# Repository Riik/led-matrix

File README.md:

# rpi-led-matrix
Python / C control for a LED matrix

# Goal
Create the software for a hardware project which can drive a LED matrix with a extendable number of rows and columns

# Hardware
To drive the rows, the MIC2981 driver IC is used. It can source up to 500mA per pin, which mean 25 columns @ 20mA / column.
To sink the columns, the TPIC6C595 is used. I needs to be able to sink one column (20mA) per pin, so for an 8 bit shift register the total IC must be able to sink 8*20mA. The TPIC6C595 is able to sink up to 100mA per pin.
The rows should multiplexed, i.e. they should not be one at the same time.

# Software
Suitable candidates:
  - PIGpio Python library using DMA control http://abyz.me.uk/rpi/pigpio/
  - Directly talking to SPI hardware in C using IOCTL

# Notes to selfs
  - If multiple rows are active, current is split / LEDS are in parallel with respect to the sinking column.
  - We probably need a resistor per sink / column

# On the subject of the LED matrix 3D model
For this model, we use two programs: OpenSCAD and FreeCAD. OpenSCAD is used to program the model. To make the model readable for KiCad:
1. Open FreeCAD
2. Select View->Workbench->OpenSCAD
3. Open the *.scad file (File->Open)
4. In Combo View->Model->Labels & Attributes->2088BS select union
5. Go to File->Export
6. Export the model as a STEP with colors (*.step *.stp)

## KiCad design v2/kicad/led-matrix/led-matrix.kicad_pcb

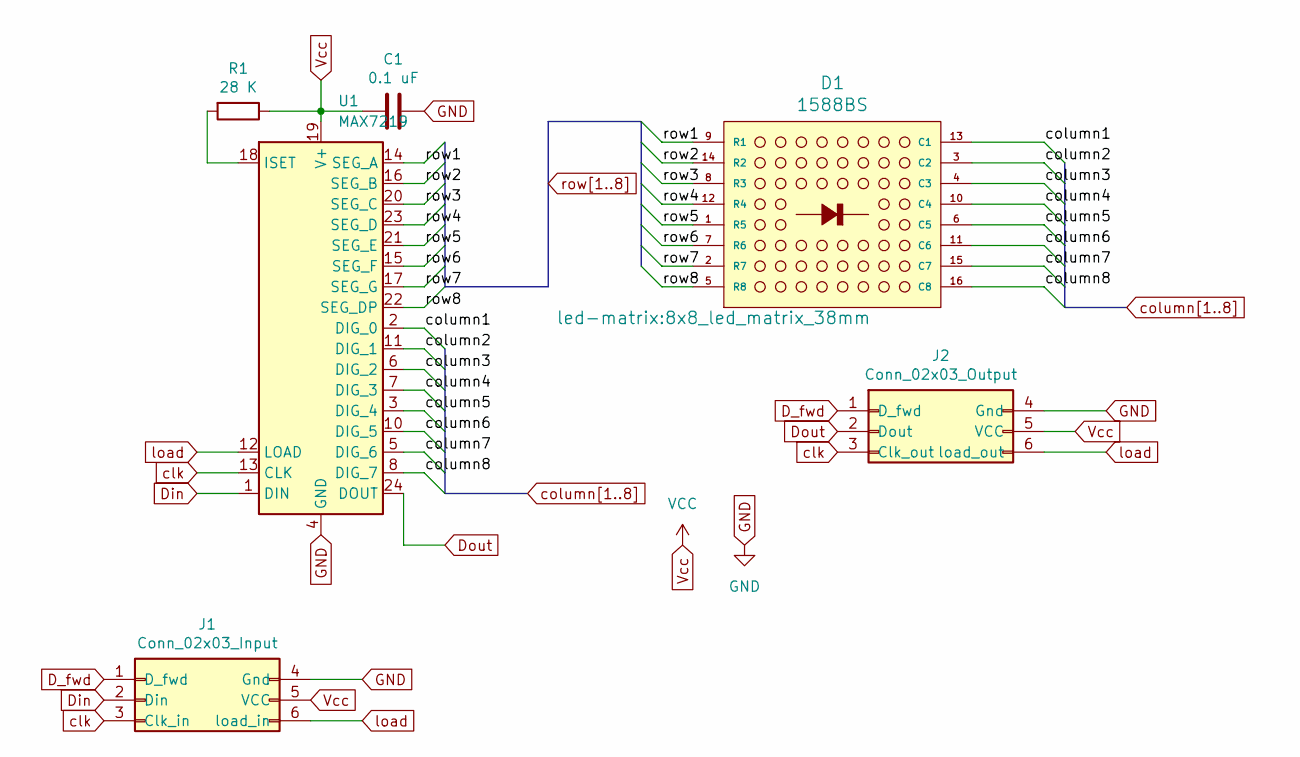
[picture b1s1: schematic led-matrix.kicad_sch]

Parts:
C1: 0.1 uF; C_1206_3216Metric_Pad1.33x1.80mm_HandSolder
D1: 1588BS; 8x8_led_matrix_38mm
J1: Conn_02x03_Input; PinSocket_2x03_P2.54mm_Horizontal
J2: Conn_02x03_Output; PinHeader_2x03_P2.54mm_Horizontal
R1: 28 K; R_1206_3216Metric_Pad1.30x1.75mm_HandSolder
U1: MAX7219; HandSolder.SOIC-24W_7.5x15.4mm_P1.27mm

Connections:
D_fwd: J1.1 (D_fwd), J2.1 (D_fwd)
Din: J1.2 (Din), U1.1 (DIN)
Dout: J2.2 (Dout), U1.24 (DOUT)
GND: C1.1, J1.4 (Gnd), J2.4 (Gnd), U1.4 (GND), U1.9 (GND)
unnamed: R1.2, U1.18 (ISET)
Vcc: C1.2, J1.5 (VCC), J2.5 (VCC), R1.1, U1.19 (V+)
clk: J1.3 (Clk_in), J2.3 (Clk_out), U1.13 (CLK)
column1: D1.13 (C1), U1.2 (DIG_0)
column2: D1.3 (C2), U1.11 (DIG_1)
column3: D1.4 (C3), U1.6 (DIG_2)
column4: D1.10 (C4), U1.7 (DIG_3)
column5: D1.6 (C5), U1.3 (DIG_4)
column6: D1.11 (C6), U1.10 (DIG_5)
column7: D1.15 (C7), U1.5 (DIG_6)
column8: D1.16 (C8), U1.8 (DIG_7)
load: J1.6 (load_in), J2.6 (load_out), U1.12 (LOAD)
row1: D1.9 (R1), U1.14 (SEG_A)
row2: D1.14 (R2), U1.16 (SEG_B)
row3: D1.8 (R3), U1.20 (SEG_C)
row4: D1.12 (R4), U1.23 (SEG_D)
row5: D1.1 (R5), U1.21 (SEG_E)
row6: D1.7 (R6), U1.15 (SEG_F)
row7: D1.2 (R7), U1.17 (SEG_G)
row8: D1.5 (R8), U1.22 (SEG_DP)

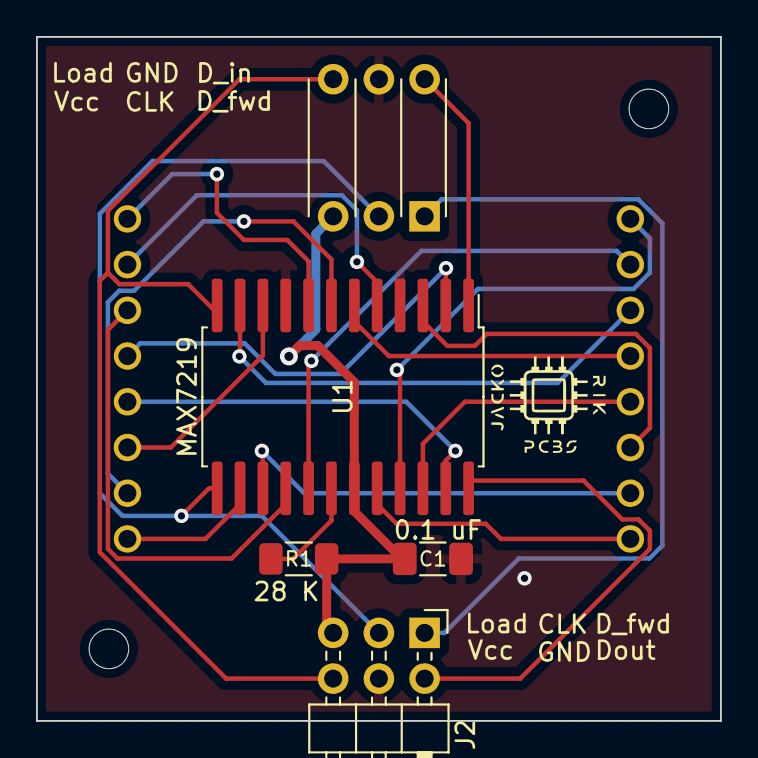
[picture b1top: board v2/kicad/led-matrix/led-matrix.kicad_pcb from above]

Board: 2 copper layers, 38.0 x 38.0 mm, 6 parts (1 on the bottom side), 24 nets.

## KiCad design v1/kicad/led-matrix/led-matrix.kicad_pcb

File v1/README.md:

# rpi-led-matrix
Python / C control for a LED matrix

# Goal
Create the software for a hardware project which can drive a LED matrix with a extendable number of rows and columns

# Hardware
To drive the rows, the MIC2981 driver IC is used. It can source up to 500mA per pin, which mean 25 columns @ 20mA / column.
To sink the columns, the TPIC6C595 is used. I needs to be able to sink one column (20mA) per pin, so for an 8 bit shift register the total IC must be able to sink 8*20mA. The TPIC6C595 is able to sink up to 100mA per pin.
The rows should multiplexed, i.e. they should not be one at the same time.

# Software
Suitable candidates:
  - PIGpio Python library using DMA control http://abyz.me.uk/rpi/pigpio/
  - Directly talking to SPI hardware in C using IOCTL

# Notes to selfs
  - If multiple rows are active, current is split / LEDS are in parallel with respect to the sinking column.
  - We probably need a resistor per sink / column

# On the subject of the LED matrix 3D model
For this model, we use two programs: OpenSCAD and FreeCAD. OpenSCAD is used to program the model. To make the model readable for KiCad:
1. Open FreeCAD
2. Select View->Workbench->OpenSCAD
3. Open the *.scad file (File->Open)
4. In Combo View->Model->Labels & Attributes->2088BS select union
5. Go to File->Export
6. Export the model as a STEP with colors (*.step *.stp)

# Selected components
 - 100 Ohm 1206 [3216 Metric]: Vishay CRCW1206100RFKEA (https://nl.farnell.com/vishay/crcw1206100rfkea/res-100r-1-0-25w-1206-thick-film/dp/1469977,
 - 10 kOhm 1206 [3216 Metric]: Vishay CRCW120610K0FKEA (https://nl.farnell.com/vishay/crcw120610k0fkea/res-10k-1-0-25w-1206-thick-film/dp/1469970RL,
 - 100 nF (0.1 uF) 1206 [3216 Metric] capacitor: Vishay VJ1206Y104KXQCW1BC (https://nl.farnell.com/vishay/vj1206y104kxqcw1bc/cap-0-1-f-10v-10-x7r-1206/dp/2896644RL,
 - Pin header male: https://nl.farnell.com/multicomp/mc34753/header-1-row-r-angle-8way/dp/1593431?ost=mc34753,
 - Pin header female: https://nl.farnell.com/samtec/ssw-108-02-g-s-ra/receptacle-2-54mm-r-a-single-8way/dp/1668368,

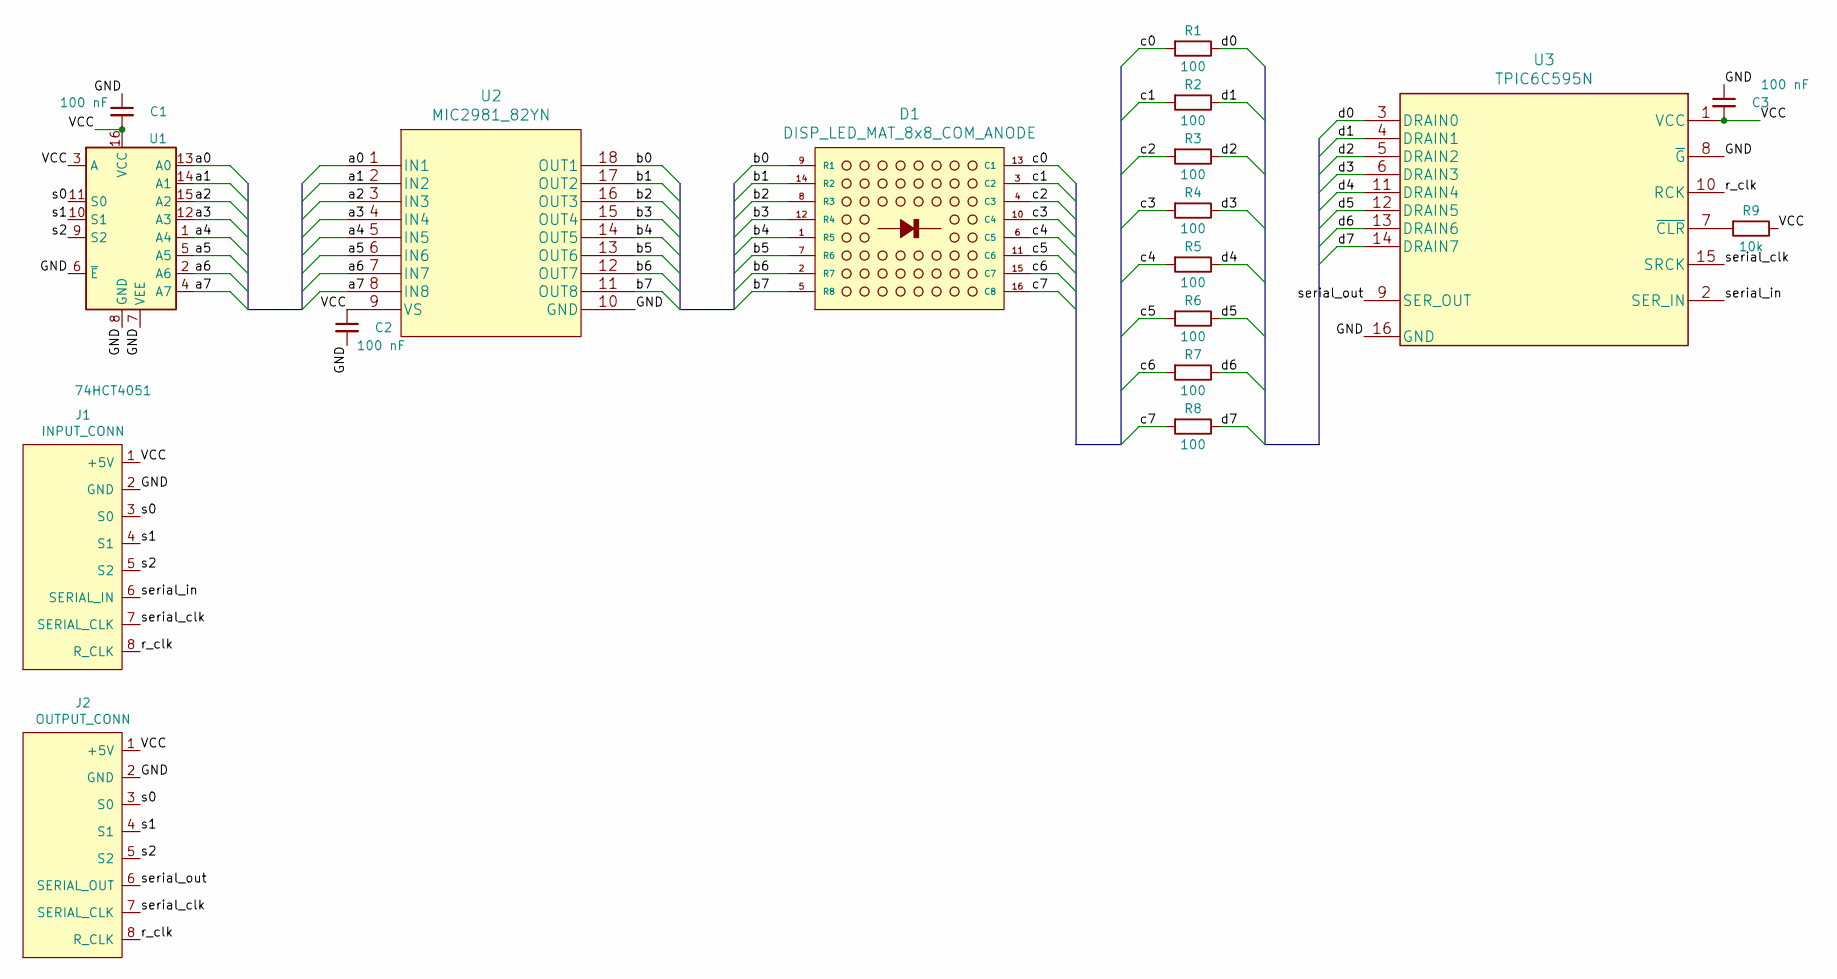
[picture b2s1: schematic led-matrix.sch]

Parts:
C1, C2, C3: 100 nF; C_1206_3216Metric_Pad1.33x1.80mm_HandSolder
D1: DISP_LED_MAT_8x8_COM_ANODE; LED_8x8_7.62MM_60.2x60.2MM
J1: INPUT_CONN; PinSocket_1x08_P2.54mm_Horizontal
J2: OUTPUT_CONN; PinHeader_1x08_P2.54mm_Horizontal
R1, R2, R3, R4, R5, R6, R7, R8: 100; R_1206_3216Metric_Pad1.30x1.75mm_HandSolder
R9: 10k; R_1206_3216Metric_Pad1.30x1.75mm_HandSolder
U1: 74HCT4051; DIP-16_W7.62mm
U2: MIC2981_82YN; DIP-18_W7.62mm
U3: TPIC6C595N; DIP-16_W7.62mm

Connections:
/GND: C1.1, C2.2, C3.1, J1.2 (GND), J2.2 (GND), U1.6 (~E), U1.7 (VEE), U1.8 (GND), U2.10 (GND), U3.8 (~G), U3.16 (GND)
/VCC: C1.2, C2.1, C3.2, J1.1 (+5V), J2.1 (+5V), R9.1, U1.3 (A), U1.16 (VCC), U2.9 (VS), U3.1 (VCC)
/a0: U1.13 (A0), U2.1 (IN1)
/a1: U1.14 (A1), U2.2 (IN2)
/a2: U1.15 (A2), U2.3 (IN3)
/a3: U1.12 (A3), U2.4 (IN4)
/a4: U1.1 (A4), U2.5 (IN5)
/a5: U1.5 (A5), U2.6 (IN6)
/a6: U1.2 (A6), U2.7 (IN7)
/a7: U1.4 (A7), U2.8 (IN8)
/b0: D1.9 (R1), U2.18 (OUT1)
/b1: D1.14 (R2), U2.17 (OUT2)
/b2: D1.8 (R3), U2.16 (OUT3)
/b3: D1.12 (R4), U2.15 (OUT4)
/b4: D1.1 (R5), U2.14 (OUT5)
/b5: D1.7 (R6), U2.13 (OUT6)
/b6: D1.2 (R7), U2.12 (OUT7)
/b7: D1.5 (R8), U2.11 (OUT8)
/c0: D1.13 (C1), R1.2
/c1: D1.3 (C2), R2.2
/c2: D1.4 (C3), R3.2
/c3: D1.10 (C4), R4.2
/c4: D1.6 (C5), R5.2
/c5: D1.11 (C6), R6.2
/c6: D1.15 (C7), R7.2
/c7: D1.16 (C8), R8.2
/d0: R1.1, U3.3 (DRAIN0)
/d1: R2.1, U3.4 (DRAIN1)
/d2: R3.1, U3.5 (DRAIN2)
/d3: R4.1, U3.6 (DRAIN3)
/d4: R5.1, U3.11 (DRAIN4)
/d5: R6.1, U3.12 (DRAIN5)
/d6: R7.1, U3.13 (DRAIN6)
/d7: R8.1, U3.14 (DRAIN7)
/r_clk: J1.8 (R_CLK), J2.8 (R_CLK), U3.10 (RCK)
/s0: J1.3 (S0), J2.3 (S0), U1.11 (S0)
/s1: J1.4 (S1), J2.4 (S1), U1.10 (S1)
/s2: J1.5 (S2), J2.5 (S2), U1.9 (S2)
/serial_clk: J1.7 (SERIAL_CLK), J2.7 (SERIAL_CLK), U3.15 (SRCK)
/serial_in: J1.6 (SERIAL_IN), U3.2 (SER_IN)
/serial_out: J2.6 (SERIAL_OUT), U3.9 (SER_OUT)
unnamed: R9.2, U3.7 (~CLR)

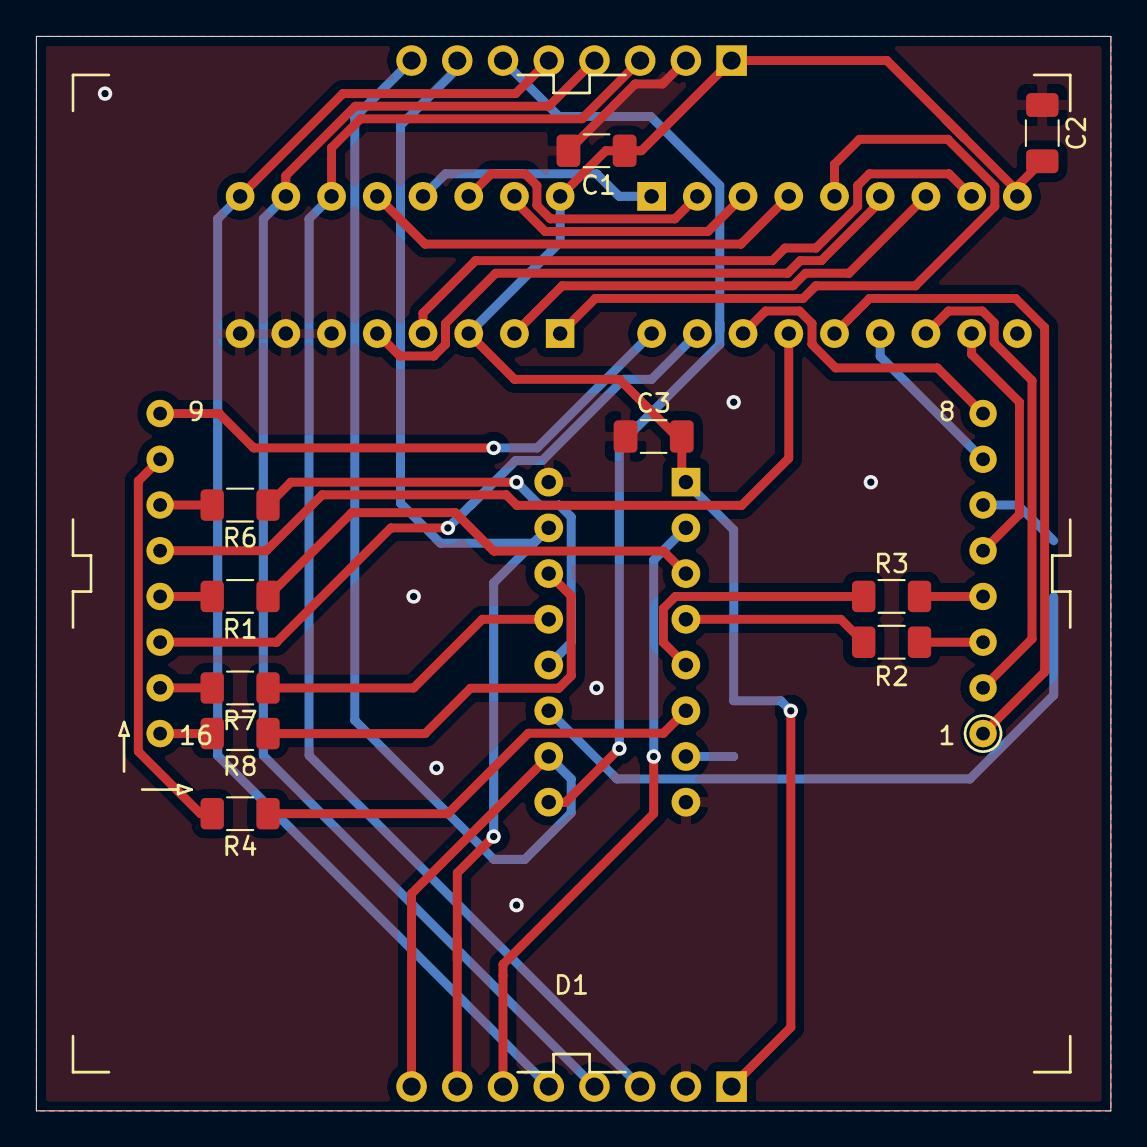
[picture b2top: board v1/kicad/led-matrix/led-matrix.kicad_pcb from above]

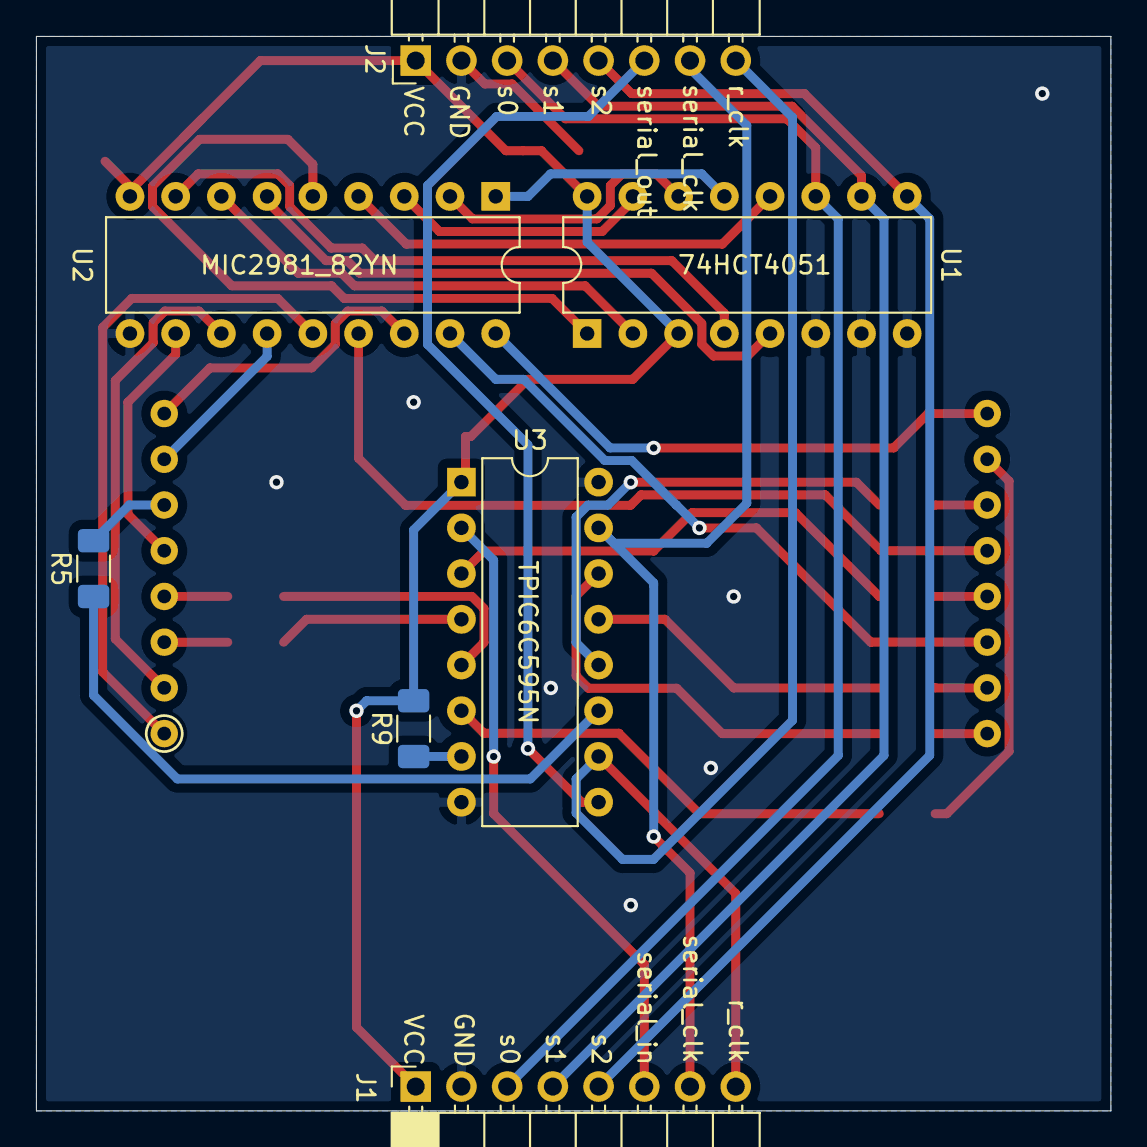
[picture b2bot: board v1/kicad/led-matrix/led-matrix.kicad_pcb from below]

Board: 2 copper layers, 59.7 x 59.7 mm, 18 parts (7 on the bottom side), 42 nets.

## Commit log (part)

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2020-10-05 Notes from the first design session
2020-11-02 change row and columns in led matrix description
2020-11-16 Add PDFs for all ICs
2020-11-16 Add arduino code for animation
2020-11-17 Add font image and conversion script
2020-12-01 move KITT_rik.ino to Arduino folder
2020-12-01 Empty eagle project
2020-12-01 new TPIC6C595 library file
2020-12-14 Add a kicad test project
2020-12-14 Remove .pro from .gitignore
2020-12-14 Add list of components
2020-12-14 Remove all traces of EAGLE
2020-12-14 Add vim temporary files to gitignore
2020-12-14 Add MIC2981 lib file to KiCAD
2020-12-14 Update schematix
2020-12-16 Remove kicad_test
2020-12-16 KiCad: Add INPUT_CONN
    From Arduino to this board
2020-12-16 KiCad: Update TPIC6C595N to match rest
2020-12-16 KiCad: Update MIC2981 to match rest
2020-12-16 KiCad: Update schematic
    Now contains main pipeline
2020-12-16 Finishes schematic
2020-12-17 Add AKNs' footprints and 3d models
2020-12-17 Update schematic, pcb
2020-12-22 Kicad: Schematic: Add capacitors and additional resistor
2020-12-22 Kicad: PCB: Add GND planes
2020-12-22 Organized components and placed headers
2020-12-28 Remove unusded models and footprints
2020-12-31 Routing left side and upper ICs
2020-12-31 Complete routing and clear up ground planes
2021-01-02 Fix double R5
2021-01-04 Tweak silk screen
2021-01-04 Gerber files for first order
2021-01-06 KiCad: Schematic: Update footprint for J1 and J2
2021-01-09 Add component information and datasheets
2021-01-12 WIP font display code and Makefile
2021-01-12 add main function
2021-01-13 Makefile compiles and uploads but code doesn't work now
2021-01-23 Update code for new LED matrix and optimize address pin timings
2021-01-23 Add scrolling text and custom input message
2021-01-23 Add serial input parsing
2021-01-25 raspberrypi: Add pabort
2021-01-25 raspberrypi: Add README.md
2021-01-25 raspberrypi: Add code opening relevant devices
2021-01-26 raspberrypi: Makefile: Remove CXXFLAGS
    No C++ here
2021-01-26 raspberrypi: inc/pabort: Include errno
2021-01-26 raspberrypi: Rework matrix driving
    Using a dual buffered approach
2021-01-27 raspberrypi: matrixDriver: We iterate over rows
2021-01-27 raspberrypi: matrixDriver: One spi_ioc_transfer is enough
2021-01-27 raspberrypi: matrixDriver: Use chip select as rck
2021-01-31 raspberrypi: main: Rework text length calculation
2021-01-31 raspberrypi: main: atomic_bool halt is static
2021-01-31 raspberrypi: main: Clear LED matrix on exit
2021-01-31 raspberrypi: matrixDriver.h: Add explanation
2021-01-31 raspberrypi: Add brightness percentage
2021-01-31 matrixDriver: Use C11 threads instead of pthreads
2021-02-07 raspberrypi: matrixDriver: Add spiMsgSize var
2021-03-27 raspberrypi: Makefile: Add -wshadow
2021-03-27 raspberrypi: Makefile: Set some warnings back to warning
2021-03-27 raspberrypi: Introduce a tileRenderer
2021-03-27 raspberrypi: Finish tileRenderer for x direction
2021-04-03 raspberrypi: tileRenderer: Remove continue in for loop
    Just start at the correct point instead of continuing until you get
    there.
2021-04-03 raspberrypi: tileRenderer: Fix support for xLen < 8
2021-04-03 raspberrypi: tileRenderer: Introduce y-axis control
2021-12-28 Move v1 files to archive folder
2021-12-28 Add documentation
2021-12-28 Add led matrix photo
2022-01-08 gitignore: Fix raspberrypi ignores
2022-01-08 v1/raspberrypi: tileRenderer.c: Further improve object merge logic
2022-01-08 v1/raspberrypy: Main: Create multiple bouncy objects
2022-01-08 v2: KiCAD: Update schematic names, datasheet
2022-01-08 v2: KiCAD: Add labels vcc, load
2022-01-08 v2: KiCAD: Finish schematic
2022-01-27 .gitignore: Add backup, auto_saved_files
2022-01-27 V2: Create female header footprint
2022-01-27 V2: Update schematic
2022-01-27 pcb first version
2022-01-28 Correct placement for headers, centred and 2.35 mm from edge
2022-02-02 Routing attempt 1
2022-02-02 fix female header
2022-02-02 Fix DRC
2022-02-02 Routing attempt 3
2022-02-04 Add logo for silkscreen
2022-02-04 add hand solder SOIC 24
2022-02-04 Changed footprint to handsoldering and added logo
2022-02-04 Aesthetics updates to PCB
2022-03-16 Cleaned up and working led control Arduino
2022-03-19 Add game of life C implementation
2022-06-05 v2:rpi:Add README
2022-06-05 v2:rpi:Move to C++
2022-06-05 v2:rpi:Introduce MatrixScreen
2022-06-05 v2:rpi:Introduce FrameLimiter
2022-06-05 v2:rpi:MatrixScreen: Guard operator() against out of range
2022-06-05 v2:rpi:matrixScreen: Remove const for copy operator
2022-06-05 v2:rpi:Introduce MatrixDriver
2022-06-05 v2:rpi:Makefile: Fix debug build location
2022-06-05 v2:rpi:First working version
2022-06-05 v2:rpi:matrixDriver: Constructor: Change param order
2022-06-05 v2:rpi:Vector2->Vector3 because of homogenous coordinates
2022-06-05 v2:rpi:Makefile: ARM-CXX -> ARM-LINUX-GNUEABIHF-CXX
2022-06-05 v2:rpi:Makefile: Update rpi4-specific flags
2022-06-05 v2:rpi:Point2D: Introduce x() y() methods
2022-06-05 v2:rpi:matrix2d.hpp: Make functions inline
2022-06-05 v2:rpi:Makefile: X86->HOST
2022-06-05 v2:rpi:matrixDriver: Check stopToken twice per second
    This reduces cpu load
2022-06-05 v2:rpi:matrixDriver: Implement size check for new matrices
2022-06-05 v2:rpi:Vector2: introduce test
2022-06-05 v2:rpi:matrixDriver: Cleanup screenToSpi
2022-06-05 v2:rpi:Makefile: ARM->RPI4 for rpi4 specifics
2022-06-05 v2:rpi:Implement Conways' game of life
2022-06-05 v2:rpi:matrix.hpp: Also include assert.h
2022-06-05 v2:rpi:Introduce gtest and nonrecursive make
2022-06-05 v2:rpi:matrixDriver: Clean up semaphore wait code
2022-06-05 v2:Rpi:Add triangle2D
2022-06-05 v2:rpi:matrixDriver: Include functional
2022-06-05 v2:rpi:matrix: Add matrix addition
2022-06-05 v2:rpi:triangle2d: createTransformedTriangle is const
2022-06-05 v2:rpi:Introduce Gfx2D::canvas
2022-06-05 v2:rpi:canvas: Split getColorOfPoint from getColorOfPixel
2022-06-05 v2:rpi:2dgfx: canvas test: Add empty frame, multiple layouts
2022-06-05 v2:rpi:Unify color enums in PixelColor
2022-06-05 v2:rpi:2dgfx: canvas: Introduce clipping space
    Now the canvas scales with the amount of led matrices, instead of
    creating a bigger window to look through.
2022-06-05 v2:rpi:Rotating square!
2022-06-05 v2:rpi:MatrixScreen: Introduce ==, != operators
2022-06-05 v2:rpi:Rename files to prevent future conflicts
2022-06-17 v2:rpi: matrixDriver: Adhere to rule of 3
2022-06-26 v2:rpi test: canvas -> canvas2d
2022-06-26 rpi:v2:matrix.hpp: Prefer pragma once
2022-07-03 v2:rpi:Compile debug with GLIBCXX_DEBUG, release with NDEBUG
2022-07-03 v2:rpi:MatrixDriver: Prefer move over copy
2022-07-04 v2:rpi:Canvas2d: generateFrame: do not return const
2022-07-06 TEMP
2022-07-09 ncurses POC
2022-07-11 v2:rpi:main.cpp: Turn screen off before exit
2022-07-11 v2:rpi:matrixDriver: Adhere to rule of 3
2022-07-11 v2:rpi:matrix.hpp: Fix operator {*|/}
    There was a mistake in the template parameter order of their return
    values
2022-07-11 v2:rpi:point2d: Introduce operator-
2022-07-11 v2:rpi:matrix.hpp: Prefer pragma once
2022-07-11 v2:rpi:SolidColorTriangle: Remove whitespace
2022-07-11 v2:rpi:Introduce texturedTriangle2d
2022-07-11 v2:rpi:matrix.hpp: Introduce operator-
2022-07-11 v2:rpi:texture2d.cpp: Remove unused header cassert
2022-07-11 v2:rpi:Introduce fontToTexture2d
2022-07-11 v2:rpi:Update main to cycle through font
2022-07-11 v2:rpi:canvas2d.cpp: generateFrame: flip loops
    Scanning over x coordinate is just more intuitive
2022-07-15 v2:rpi:Move framelimiter to main
2022-07-15 rpi4:v2:matrix/rules.mk: 2DGLX->MATRIX
2022-07-15 v2:rpi:Makefile:Add host-release, host-debug target
2022-07-17 Alternative Matrixdriver for ncurses with empty implementation
2022-07-17 first buggy version
2022-07-20 Cleaned implementation matrixdriver.cpp
2022-07-20 Remove copy of old matrixdriver
2022-07-20 Added some comments and added makefile flags back in
2022-07-20 Remove ncurses POC directory
2022-07-20 Restore main.cpp from main branch
2022-07-20 asdfkj
2022-08-14 v2:rpi:matrix/rules.mk: 2DGLX->MATRIX
2022-08-14 v2:rpi:Introduce boundaryBox2d
2022-08-14 v2:rpi:canvas2d:Use boundarybox for clipping space
    This boundarybox checks if the CanvasDrawable2d states it is inside the
    clipping space. If the CanvasDrawable2d is not inside the clipping space
    we never have to consider it again. Note that the CanvasDrawable2d is
    not guaranteed to return false if it is outside of clipping space. But
    this is better than nothing at all
2022-08-14 v2:rpi:matrixDriver: Shutdown ledmatrices on destruction
2022-08-14 v2:rpi: Makefile: host->host-build
2022-08-14 v2:rpi: Triangles get boundaryboxes
2022-08-14 v2:rpi:Add profile target
2022-08-18 v2:rpi: Introduce argument parsing
2022-08-18 v2:rpi: argParsing: Add test
2022-08-20 v2:rpi: frameLimiter: const uint32_t -> uint_fast32_t
2022-08-20 v2:rpi: matrixDriver: Prefer pass-by-value over pass-by-reference
2022-08-20 v2:rpi: str2number: int64_t -> long long
2022-10-17 v2:rpi: Add archflags to linker stage
    This could help in optimizations, such as only including code for the
    specific platform.
2022-10-17 v2:rpi: Add class numListStats
2022-10-17 v2:rpi: Introduce MatrixDriver interface
    This paves the way for multiple matrixdrivers to exist
2022-10-17 v2:rpi: Disable matrixDriverSpi under APPLE
    The SPI stuff is Linux specific and therefore will not work under Apple.
    Make sure it does not get compiled.
2022-10-17 v2:rpi: MatrixDriverSpi: Remove unused includes
2023-02-13 Fast roll and slowdown
2023-02-13 Update triangles with new random numbers
2023-02-13 XKCD 221
2023-02-13 Make number of sides configurable
2023-02-13 Center single digits
2023-02-13 Add easter egg
2023-02-13 .idea in gitignore
2023-04-07 YEEET
2023-04-11 First version of IoController class; doesn't compile yet
2023-04-11 Working version of wait for button press to roll
2023-04-12 Cosmetic changes
2023-04-12 remove bulk line events
2023-04-13 test with event_read
2023-04-14 v2:rpi: Use custom semaphore implementation
    std::binary_semaphore is not available yet
2023-04-14 v2:rpi: Rework Makefiles
2023-04-15 v2:rpi: Select matrix driver via args
    Unless APPLE, unfortunately :(
2023-04-15 v2:rpi: Update README
2023-04-30 v2:rpi: flags.mk: Add -Wdouble-promotion
2023-04-30 v2:rpi:flags.mk: ggdb -> ggdb3
2023-04-30 v2:rpi:flags.mk: Introduce sanitizers
2023-05-11 TENP
2023-05-17 TEMPTEMPTEMP
2023-05-17 v2:rpi: matrixDriverNcurses: ncurses also works for ARM
2023-05-17 also remove arm flag from cpp file
2023-05-17 main: set screensize to 1,1
2023-05-17 Chomp multiple events
2023-05-17 -1 is also good enough to stop
2023-05-17 Well, it was not NULL aware after all.
2023-05-17 First chomp, then wait
2023-05-18 v2:rpi: Introduce TextScroller as seperate unit
2023-05-18 v2:rpi: Add --text
2023-05-21 v2:rpi: Add --textSpeed
2023-05-21 v2:rpi:predefined.mk: Remove host_ from dirs
2023-05-21 Inntroduce stdinPoller
2023-05-21 v2:rpi:Introduce dice generator
2023-05-21 v2:rpi: Rewrite ioController into inputEventHandler
2023-05-21 v2:rpi: Add stdinEventHandler
2023-05-27 v2:rpi: Move diceGenerator to subprogram
2023-05-27 v2:rpi: diceGenerator: Introduce input event selection
2023-05-27 v2:rpi: Allow subprogram selection
2024-05-23 v2 riscv: Update linker_script
2024-05-23 v2 riscv: Makefile, remove echo, remove bin on clean
2024-05-23 v2 riscv: rules.mk: Allow full C++ capabilities
    For now
2024-05-23 v2 riscv: linker_script: Get rid of fini array
    The program is never supposed to finish, so we do not expect to run the
    fini functions
2024-05-23 v2 riscv: Add matrixScreen and pixelColor
2024-05-23 v2 riscv: Optimize for size
2024-05-23 v2 riscv: Introduce matrixDriver
2024-05-23 v2 riscv matrixDriver: Add const, setBrightness
2024-05-23 v2 riscv: Implement 2dgfx
2024-06-23 v2 riscv: Switch to stdc++_nano libs
2024-06-23 v2 riscv: Add unused-function to no-error list
2024-11-14 V2 riscv: Get rid of linker_script trick
2025-04-05 V2 riscv: Update HAL
2025-04-05 V2 riscv Makefile: Switch ti rv32im
2025-04-05 V2 riscv: Set optimization to O3
2025-04-05 V2 riscv main.cpp: Prefer emplace_back
2025-04-05 V2 riscv main.cpp: Add some benchmarking
2026-01-09 v2 riscv: Replace hal with submodule
